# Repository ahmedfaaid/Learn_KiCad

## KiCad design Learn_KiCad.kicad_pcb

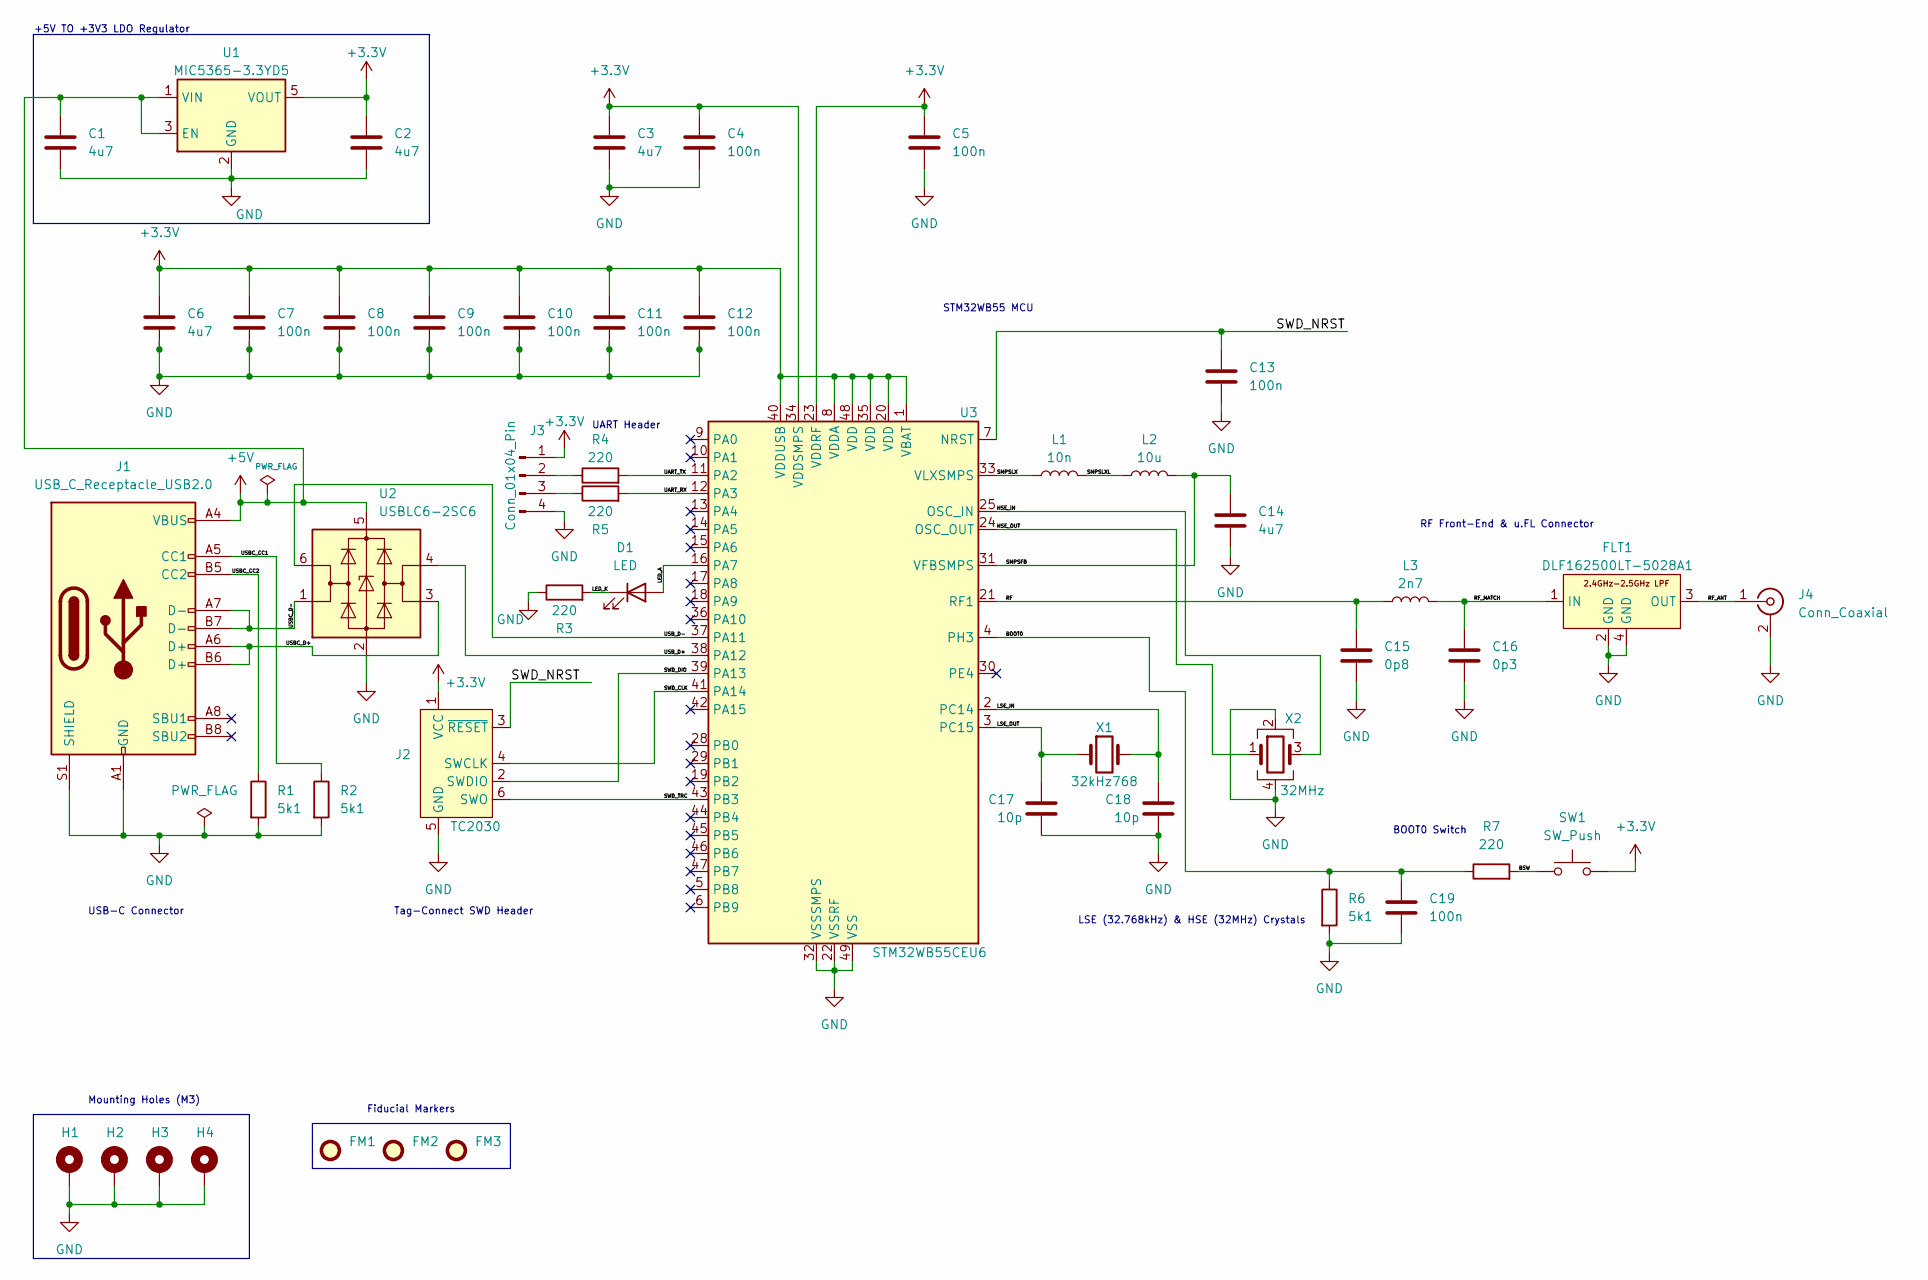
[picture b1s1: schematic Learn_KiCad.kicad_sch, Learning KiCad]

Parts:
C1, C2, C3, C6, C14: 4u7; C_0603_1608Metric; Manufacturer Part Number 0603YD475MAT2A
C4, C5, C7, C8, C9, C10, C11, C12, C13, C19: 100n; C_0402_1005Metric; Manufacturer Part Number 04023C102KAZ2A
C15: 0p8; C_0402_1005Metric; Manufacturer Part Number GRM1555C2AR80BA01D
C16: 0p3; C_0402_1005Metric; Manufacturer Part Number GRM1555C1HR30WA01D
C17, C18: 10p; C_0402_1005Metric; Manufacturer Part Number 04025A100JAT4A
D1: LED; LED_0402_1005Metric; Manufacturer Part Number 150040RS73240
FLT1: DLF162500LT-5028A1; Manufacturer Part Number DLF162500LT-5028A1
FM1, FM2, FM3: Fiducial; Fiducial_1mm_Mask2mm
H1, H2, H3, H4: MountingHole_Pad; MountingHole_2.2mm_M2_Pad_Via
J1: USB_C_Receptacle_USB2.0; USB_C_Receptacle_GCT_USB4105-xx-A_16P_TopMnt_Horizontal; Manufacturer Part Number USB4105-GF-A
J2: TC2030; Tag-Connect_TC2030-IDC-FP_2x03_P1.27mm_Vertical
J3: Conn_01x04_Pin; Molex_PicoBlade_53048-0410_1x04_P1.25mm_Horizontal; Manufacturer Part Number 53048-0410
J4: Conn_Coaxial; U.FL_Hirose_U.FL-R-SMT-1_Vertical; Manufacturer Part Number U.FL-R-SMT(01)
L1: 10n; L_0402_1005Metric; Manufacturer Part Number LQG15WZ10NJ02D
L2: 10u; L_0805_2012Metric; Manufacturer Part Number LQM21DH100M70L
L3: 2n7; L_0402_1005Metric; Manufacturer Part Number LQG15HS2N7S02D
R1, R2, R6: 5k1; R_0402_1005Metric; Manufacturer Part Number RC0402FR-075K1L
R3, R4, R5, R7: 220; R_0402_1005Metric; Manufacturer Part Number RC0402FR-07220RL
SW1: SW_Push; SW_SPST_CK_RS282G05A3; Manufacturer Part Number RS282G05A3SMRT
U1: MIC5365-3.3YD5; SOT-23-5; Manufacturer Part Number MIC5365-3.3YD5-TR
U2: USBLC6-2SC6; SOT-23-6; Manufacturer Part Number SBLC6-2SC6
U3: STM32WB55CEU6; QFN-48-1EP_7x7mm_P0.5mm_EP5.6x5.6mm; Manufacturer Part Number STM32WB55CEU6
X1: 32kHz768; Crystal_SMD_2012-2Pin_2.0x1.2mm; Manufacturer Part Number NX2012SA-32.768K-STD-MUB-1
X2: 32MHz; Crystal_SMD_2016-4Pin_2.0x1.6mm; Manufacturer Part Number NX2016SA-32M-EXS00A-CS06465\

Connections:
+3.3V: C2.1, C3.1, C4.1, C5.1, C6.1, C7.1, C8.1, C9.1, C10.1, C11.1, C12.1, J2.1 (VCC), J3.1, SW1.2, U1.5 (VOUT), U3.1 (VBAT), U3.8 (VDDA), U3.20 (VDD), U3.23 (VDDRF), U3.34 (VDDSMPS), U3.35 (VDD), U3.40 (VDDUSB), U3.48 (VDD)
+5V: C1.1, J1.A4 (VBUS), J1.A9 (VBUS), J1.B4 (VBUS), J1.B9 (VBUS), U1.1 (VIN), U1.3 (EN), U2.5 (VBUS)
/BOOT0: C19.1, R6.1, R7.1, U3.4 (PH3)
/BSW: R7.2, SW1.1
/HSE_IN: U3.25 (OSC_IN), X2.3
/HSE_OUT: U3.24 (OSC_OUT), X2.1
/LED_A: D1.2 (A), U3.16 (PA7)
/LED_K: D1.1 (K), R3.2
/LSE_IN: C18.1, U3.2 (PC14), X1.2
/LSE_OUT: C17.1, U3.3 (PC15), X1.1
/RF: C15.1, L3.1, U3.21 (RF1)
/RF_ANT: FLT1.3 (OUT), J4.1 (In)
/RF_MATCH: C16.1, FLT1.1 (IN), L3.2
/SMPSFB: C14.1, L2.2, U3.31 (VFBSMPS)
/SMPSLX: L1.1, U3.33 (VLXSMPS)
/SMPSLXL: L1.2, L2.1
/SWD_CLK: J2.4 (SWCLK), U3.41 (PA14)
/SWD_DIO: J2.2 (SWDIO), U3.39 (PA13)
/SWD_NRST: C13.1, J2.3 (~RESET), U3.7 (NRST)
/SWD_TRC: J2.6 (SWO), U3.43 (PB3)
/UART_RX: R5.2, U3.12 (PA3)
/UART_TX: R4.2, U3.11 (PA2)
/USBC_CC1: J1.A5 (CC1), R2.1
/USBC_CC2: J1.B5 (CC2), R1.1
/USBC_D+: J1.A6 (D+), J1.B6 (D+), U2.3 (I/O2)
/USBC_D-: J1.A7 (D-), J1.B7 (D-), U2.1 (I/O1)
/USB_D+: U2.4 (I/O2), U3.38 (PA12)
/USB_D-: U2.6 (I/O1), U3.37 (PA11)
GND: C1.2, C2.2, C3.2, C4.2, C5.2, C6.2, C7.2, C8.2, C9.2, C10.2, C11.2, C12.2, C13.2, C14.2, C15.2, C16.2, C17.2, C18.2, C19.2, FLT1.2 (GND), FLT1.4 (GND), H1.1, H2.1, H3.1, H4.1, J1.A1 (GND), J1.A12 (GND), J1.B1 (GND), J1.B12 (GND), J1.S1 (SHIELD), J2.5 (GND), J3.4, J4.2 (Ext), R1.2, R2.2, R3.1, R6.2, U1.2 (GND), U2.2 (GND), U3.22 (VSSRF), U3.32 (VSSSMPS), U3.49 (VSS), X2.2, X2.4
unnamed: J3.2, R4.1
unnamed: J3.3, R5.1

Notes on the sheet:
Fiducial Markers
UART Header
Tag-Connect SWD Header
USB-C Connector
+5V TO +3V3 LDO Regulator
Mounting Holes (M3)
RF Front-End & u.FL Connector
LSE (32.768kHz) & HSE (32MHz) Crystals
BOOT0 Switch
STM32WB55 MCU

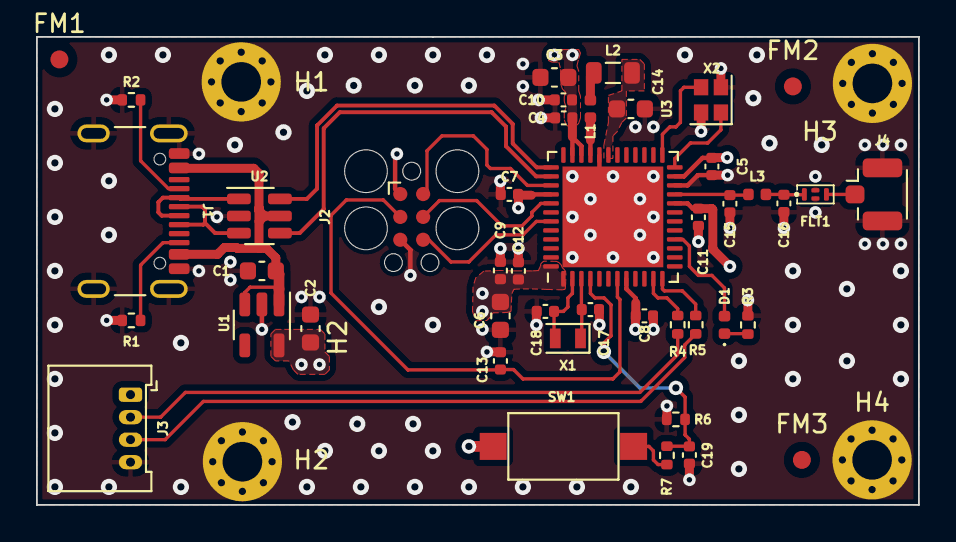
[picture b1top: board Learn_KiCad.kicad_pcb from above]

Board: 4 copper layers, 49.0 x 26.0 mm, 48 parts (0 on the bottom side), 31 nets.

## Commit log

2024-01-09 2024-01-09 5:03
2024-01-10 2024-01-09 22:03
2024-01-14 2024-01-13 22:28
2024-02-01 2024-02-01 8:33am
2024-02-16 2024-02-15 21:52
2024-03-16 2024-03-16 14:17
2024-04-07 2024-04-07 13:56
